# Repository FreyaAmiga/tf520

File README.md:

Terrible Fire 68020 "Accelerator"
=================================

** WARNING THIS IS BETA AT THE MOMENT

This repository contains all the files needed to produce a copy of my accelerator board.

The CPLD Required is a XC9532XL-VQ44

Everything in this repository is released under the GNU GPLv2. You may create or base commercial PCBs from the work in this repository but you must make the sources for all derivative work available. 

Firmware / Requirements
------------

  * Xilinx ISE, 14.7 (the final version - other versions may work but this is the one I support)
  * JTAG Adaptor

PCB Manufacture
---------------

You may get any PCB manufacturer to produce the board for you. The board is 2-layer. I recommend DirtyPCBs 

This link takes you to a store to buy them 

http://dirtypcbs.com/store/designer/details/12476/1120/sl520-rev3-zip

To populate a PCB you will likely need the following tools.

  * Soldering Station (with hot air rework and an iron - probably with a few tips)
  * Stereo Microscope (or similar for soldering under)
  * Bench Power Supply (to verify the regulator circuit)
 
There will be those with more experience and great eyesight that could manage it with just a soldering iron but I am trying to be realistic here.

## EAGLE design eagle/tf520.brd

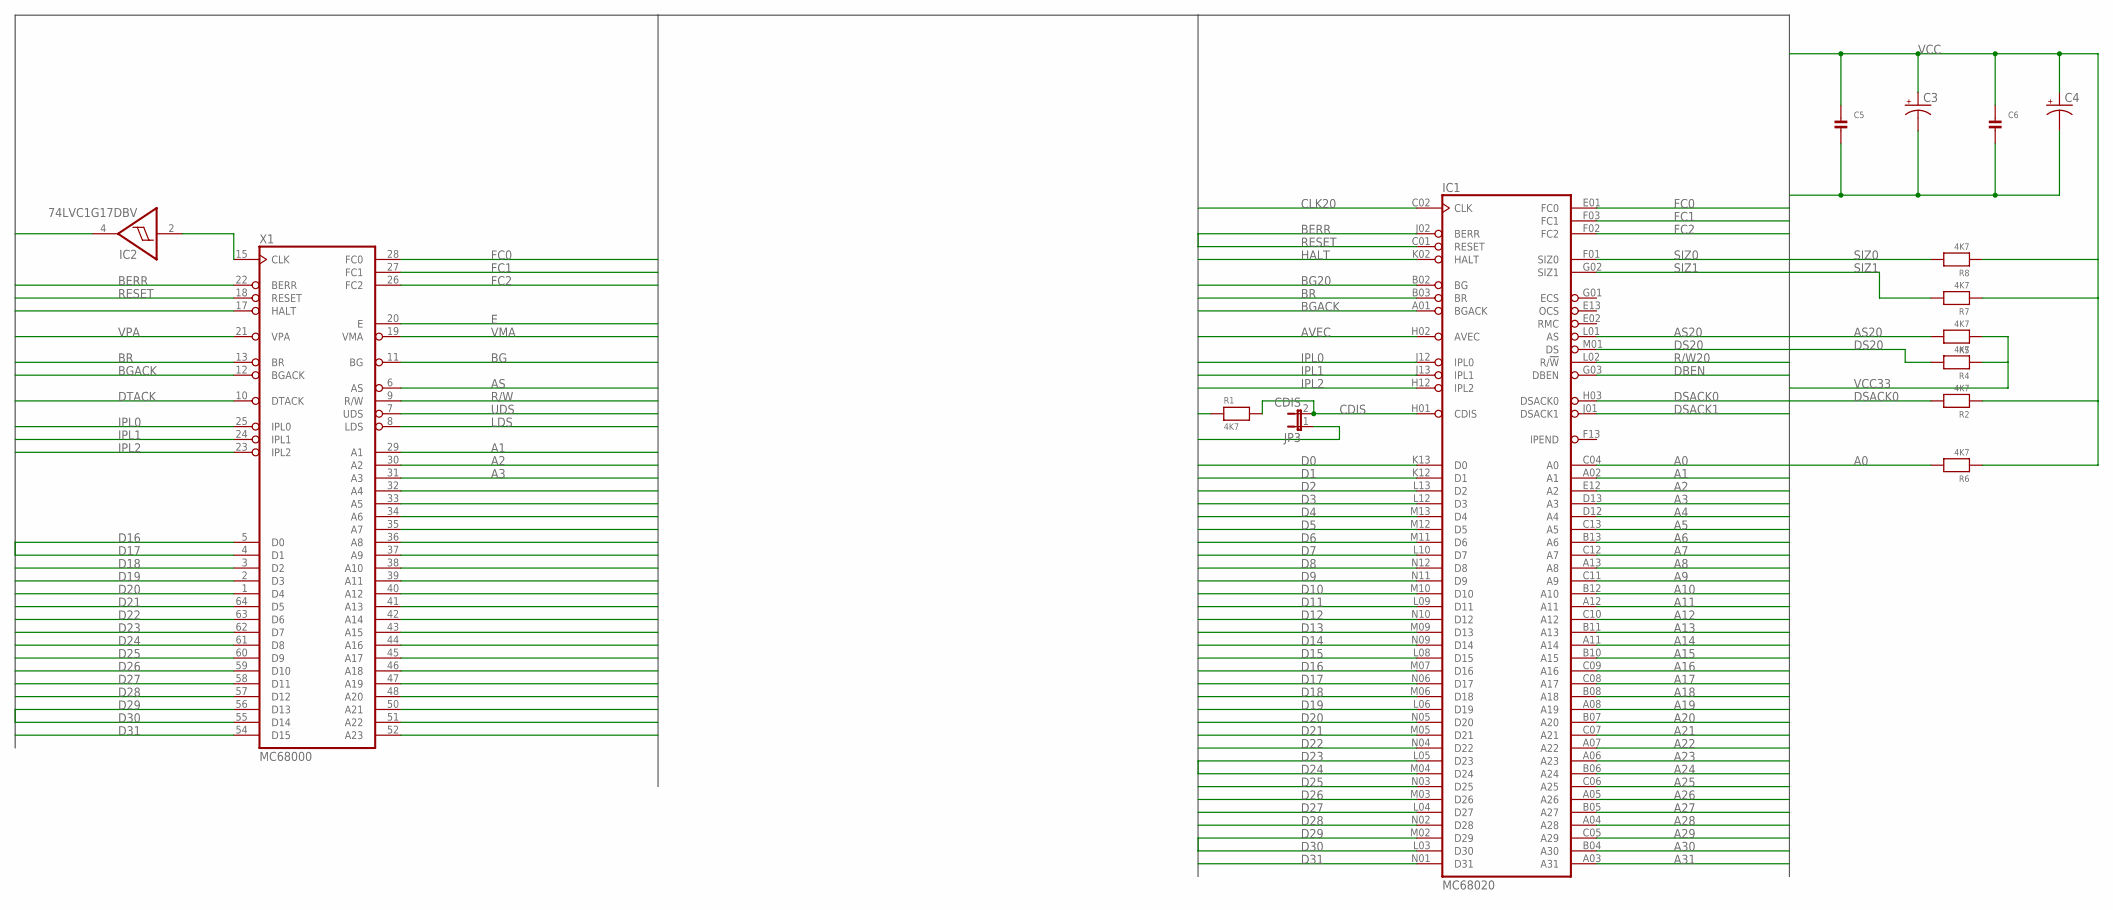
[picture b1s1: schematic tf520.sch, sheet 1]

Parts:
C3, C4: CAP_POLD; PANASONIC_D
C5, C6: CAP_CERAMIC1206; 1206
IC1: MC68020; MPGA114
IC2: 74LVC1G17DBV; SOT23-5
JP3: CDIS; 1X02
R1, R2, R4, R5, R6, R7, R8: 4K7; 1206
X1: MC68000; DIL64

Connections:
A0: IC1.C04 (A0), R6.2; also elsewhere on the board
A1: IC1.A02 (A1), X1.29 (A1)
A2: IC1.E12 (A2), X1.30 (A2)
A3: IC1.D13 (A3), X1.31 (A3)
A4: IC1.D12 (A4), X1.32 (A4)
A5: IC1.C13 (A5), X1.33 (A5)
A6: IC1.B13 (A6), X1.34 (A6)
A7: IC1.C12 (A7), X1.35 (A7)
A8: IC1.A13 (A8), X1.36 (A8)
A9: IC1.C11 (A9), X1.37 (A9)
A10: IC1.B12 (A10), X1.38 (A10)
A11: IC1.A12 (A11), X1.39 (A11)
A12: IC1.C10 (A12), X1.40 (A12)
A13: IC1.B11 (A13), X1.41 (A13)
A14: IC1.A11 (A14), X1.42 (A14)
A15: IC1.B10 (A15), X1.43 (A15)
A16: IC1.C09 (A16), X1.44 (A16); also elsewhere on the board
A17: IC1.C08 (A17), X1.45 (A17); also elsewhere on the board
A18: IC1.B08 (A18), X1.46 (A18); also elsewhere on the board
A19: IC1.A08 (A19), X1.47 (A19); also elsewhere on the board
A20: IC1.B07 (A20), X1.48 (A20)
A21: IC1.C07 (A21), X1.50 (A21)
A22: IC1.A07 (A22), X1.51 (A22)
A23: IC1.A06 (A23), X1.52 (A23)
A24: IC1.B06 (A24)
A25: IC1.C06 (A25)
A26: IC1.A05 (A26)
A27: IC1.B05 (A27)
A28: IC1.A04 (A28)
A29: IC1.C05 (A29)
A30: IC1.B04 (A30)
A31: IC1.A03 (A31)
AS: X1.6 (AS); also elsewhere on the board
AS20: IC1.L01 (AS), R5.2; also elsewhere on the board
AVEC: IC1.H02 (AVEC); also elsewhere on the board
BERR: IC1.J02 (BERR), X1.22 (BERR); also elsewhere on the board
BG: X1.11 (BG); also elsewhere on the board
BG20: IC1.B02 (BG); also elsewhere on the board
BGACK: IC1.A01 (BGACK), X1.12 (BGACK); also elsewhere on the board
BR: IC1.B03 (BR), X1.13 (BR)
CDIS: IC1.H01 (CDIS), JP3.2, R1.2
CLK7M: IC2.4 (O); also elsewhere on the board
CLK7M_RAW: IC2.2 (I), X1.15 (CLK)
CLK20: IC1.C02 (CLK); also elsewhere on the board
D0: IC1.K13 (D0)
D1: IC1.K12 (D1)
D2: IC1.L13 (D2)
D3: IC1.L12 (D3)
D4: IC1.M13 (D4)
D5: IC1.M12 (D5)
D6: IC1.M11 (D6)
D7: IC1.L10 (D7)
D8: IC1.N12 (D8)
D9: IC1.N11 (D9)
D10: IC1.M10 (D10)
D11: IC1.L09 (D11)
D12: IC1.N10 (D12)
D13: IC1.M09 (D13)
D14: IC1.N09 (D14)
D15: IC1.L08 (D15)
D16: IC1.M07 (D16), X1.5 (D0)
D17: IC1.N06 (D17), X1.4 (D1)
D18: IC1.M06 (D18), X1.3 (D2)
D19: IC1.L06 (D19), X1.2 (D3)
D20: IC1.N05 (D20), X1.1 (D4)
D21: IC1.M05 (D21), X1.64 (D5)
D22: IC1.N04 (D22), X1.63 (D6)
D23: IC1.L05 (D23), X1.62 (D7)
D24: IC1.M04 (D24), X1.61 (D8)
D25: IC1.N03 (D25), X1.60 (D9)
D26: IC1.M03 (D26), X1.59 (D10)
D27: IC1.L04 (D27), X1.58 (D11)
D28: IC1.N02 (D28), X1.57 (D12)
D29: IC1.M02 (D29), X1.56 (D13)
D30: IC1.L03 (D30), X1.55 (D14)
D31: IC1.N01 (D31), X1.54 (D15)
DBEN: IC1.G03 (DBEN)
DS20: IC1.M01 (DS), R4.2; also elsewhere on the board
DSACK0: IC1.H03 (DSACK0), R2.2
DSACK1: IC1.J01 (DSACK1); also elsewhere on the board
DTACK: X1.10 (DTACK); also elsewhere on the board
E: X1.20 (E); also elsewhere on the board
FC0: IC1.E01 (FC0), X1.28 (FC0); also elsewhere on the board
FC1: IC1.F03 (FC1), X1.27 (FC1); also elsewhere on the board
FC2: IC1.F02 (FC2), X1.26 (FC2); also elsewhere on the board
GND: C3.-, C4.-, C5.2, C6.2, IC1.A10 (GND), IC1.B01 (GND), IC1.B09 (GND), IC1.C03 (GND), IC1.F12 (GND), IC1.G12 (GND), IC1.H13 (GND), IC1.J03 (GND), IC1.K01 (GND), IC1.K03 (GND), IC1.L07 (GND), IC1.L11 (GND), IC1.N07 (GND), IC2.3 (GND), JP3.1, X1.16 (GND), X1.53 (GND); also elsewhere on the board
HALT: IC1.K02 (HALT), X1.17 (HALT); also elsewhere on the board
IPL0: IC1.J12 (IPL0), X1.25 (IPL0)
IPL1: IC1.J13 (IPL1), X1.24 (IPL1)
IPL2: IC1.H12 (IPL2), X1.23 (IPL2)
LDS: X1.8 (LDS); also elsewhere on the board
R/W: X1.9 (R/W); also elsewhere on the board
R/W20: IC1.L02 (R/!W); also elsewhere on the board
RESET: IC1.C01 (RESET), X1.18 (RESET); also elsewhere on the board
SIZ0: IC1.F01 (SIZ0), R8.2; also elsewhere on the board
SIZ1: IC1.G02 (SIZ1), R7.2; also elsewhere on the board
UDS: X1.7 (UDS); also elsewhere on the board
VCC: C3.+, C4.+, C5.1, C6.1, IC1.A09 (VCC), IC1.D01 (VCC), IC1.D02 (VCC), IC1.D03 (VCC), IC1.E03 (VCC), IC1.G11 (VCC), IC1.G13 (VCC), IC1.M08 (VCC), IC1.N08 (VCC), IC1.N13 (VCC), IC2.5 (VCC), R1.1, R2.1, R6.1, R7.1, R8.1, X1.14 (VCC), X1.49 (VCC); also elsewhere on the board
VCC33: R4.1, R5.1; also elsewhere on the board
VMA: X1.19 (VMA); also elsewhere on the board
VPA: X1.21 (VPA); also elsewhere on the board

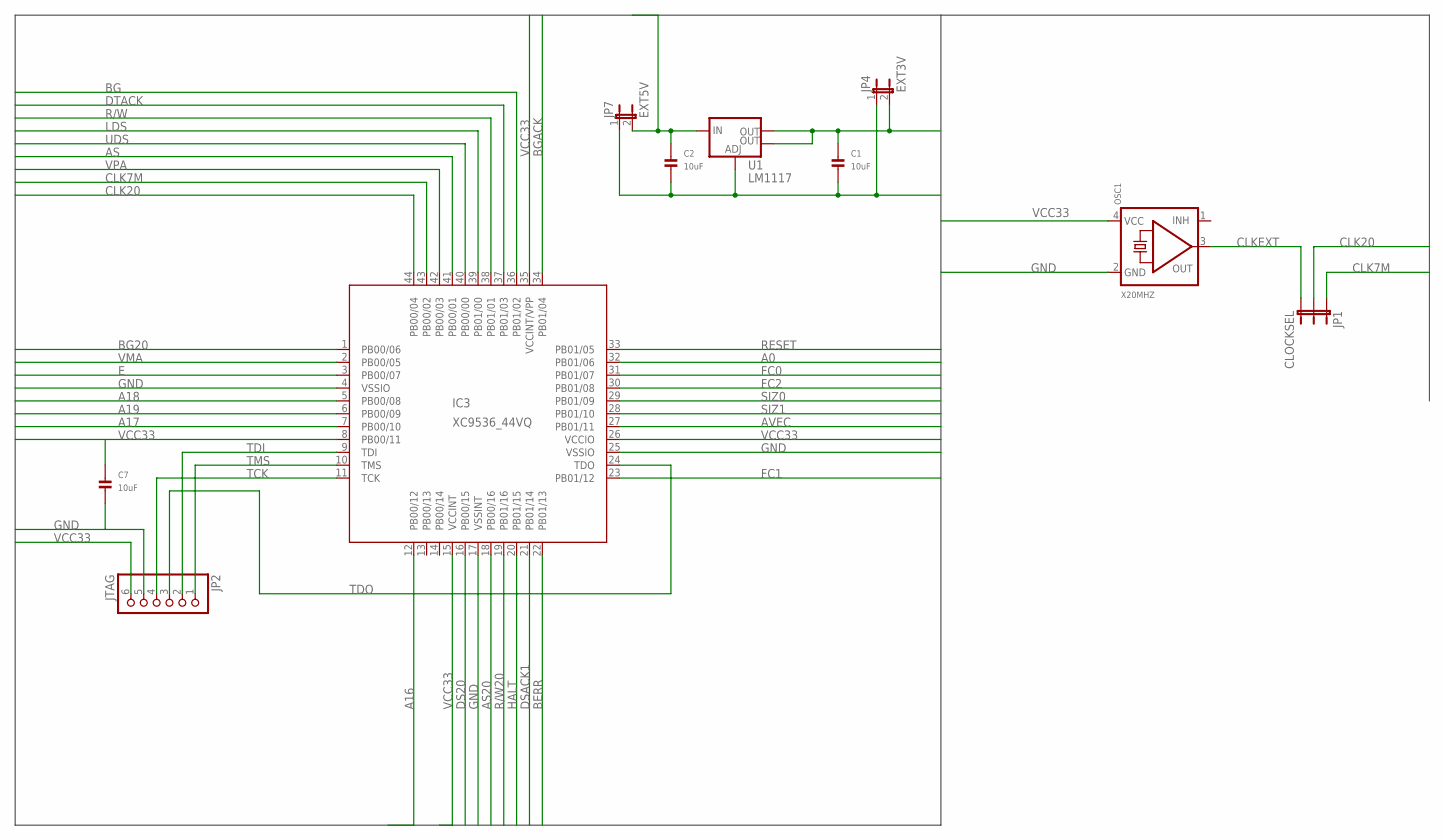
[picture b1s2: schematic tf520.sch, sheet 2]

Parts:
C1, C2, C7: 10uF; 1206
IC3: XC9536_44VQ; SQFP-S-10X10-44
JP1: CLOCKSEL; 1X03
JP2: JTAG; 1X06_ROUND
JP4: EXT3V; 1X02
JP7: EXT5V; JP1
OSC1: X20MHZ; OSC_7X5MM
U1: LM1117; SOT223

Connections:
A0: IC3.32 (PB01/06); also elsewhere on the board
A16: IC3.12 (PB00/12); also elsewhere on the board
A17: IC3.7 (PB00/10); also elsewhere on the board
A18: IC3.5 (PB00/08); also elsewhere on the board
A19: IC3.6 (PB00/09); also elsewhere on the board
AS: IC3.41 (PB00/01); also elsewhere on the board
AS20: IC3.18 (PB00/16); also elsewhere on the board
AVEC: IC3.27 (PB01/11); also elsewhere on the board
BERR: IC3.22 (PB01/13); also elsewhere on the board
BG: IC3.36 (PB01/02); also elsewhere on the board
BG20: IC3.1 (PB00/06); also elsewhere on the board
BGACK: IC3.34 (PB01/04); also elsewhere on the board
CLK7M: IC3.43 (PB00/02), JP1.1; also elsewhere on the board
CLK20: IC3.44 (PB00/04), JP1.2; also elsewhere on the board
CLKEXT: JP1.3, OSC1.3 (OUT)
DS20: IC3.16 (PB00/15); also elsewhere on the board
DSACK1: IC3.21 (PB01/14); also elsewhere on the board
DTACK: IC3.37 (PB01/03); also elsewhere on the board
E: IC3.3 (PB00/07); also elsewhere on the board
FC0: IC3.31 (PB01/07); also elsewhere on the board
FC1: IC3.23 (PB01/12); also elsewhere on the board
FC2: IC3.30 (PB01/08); also elsewhere on the board
GND: C1.2, C2.2, C7.2, IC3.4 (VSSIO), IC3.17 (VSSINT), IC3.25 (VSSIO), JP2.5, JP4.1, JP7.1, OSC1.2 (GND), U1.1 (ADJ); also elsewhere on the board
HALT: IC3.20 (PB01/15); also elsewhere on the board
LDS: IC3.39 (PB01/00); also elsewhere on the board
R/W: IC3.38 (PB01/01); also elsewhere on the board
R/W20: IC3.19 (PB01/16); also elsewhere on the board
RESET: IC3.33 (PB01/05); also elsewhere on the board
SIZ0: IC3.29 (PB01/09); also elsewhere on the board
SIZ1: IC3.28 (PB01/10); also elsewhere on the board
TCK: IC3.11 (TCK), JP2.4
TDI: IC3.9 (TDI), JP2.2
TDO: IC3.24 (TDO), JP2.3
TMS: IC3.10 (TMS), JP2.1
UDS: IC3.40 (PB00/00); also elsewhere on the board
VCC: C2.1, JP7.2, U1.3 (IN); also elsewhere on the board
VCC33: C1.1, C7.1, IC3.8 (PB00/11), IC3.15 (VCCINT), IC3.26 (VCCIO), IC3.35 (VCCINT/VPP), JP2.6, JP4.2, OSC1.4 (VCC), U1.2 (OUT), U1.4 (OUT); also elsewhere on the board
VMA: IC3.2 (PB00/05); also elsewhere on the board
VPA: IC3.42 (PB00/03); also elsewhere on the board

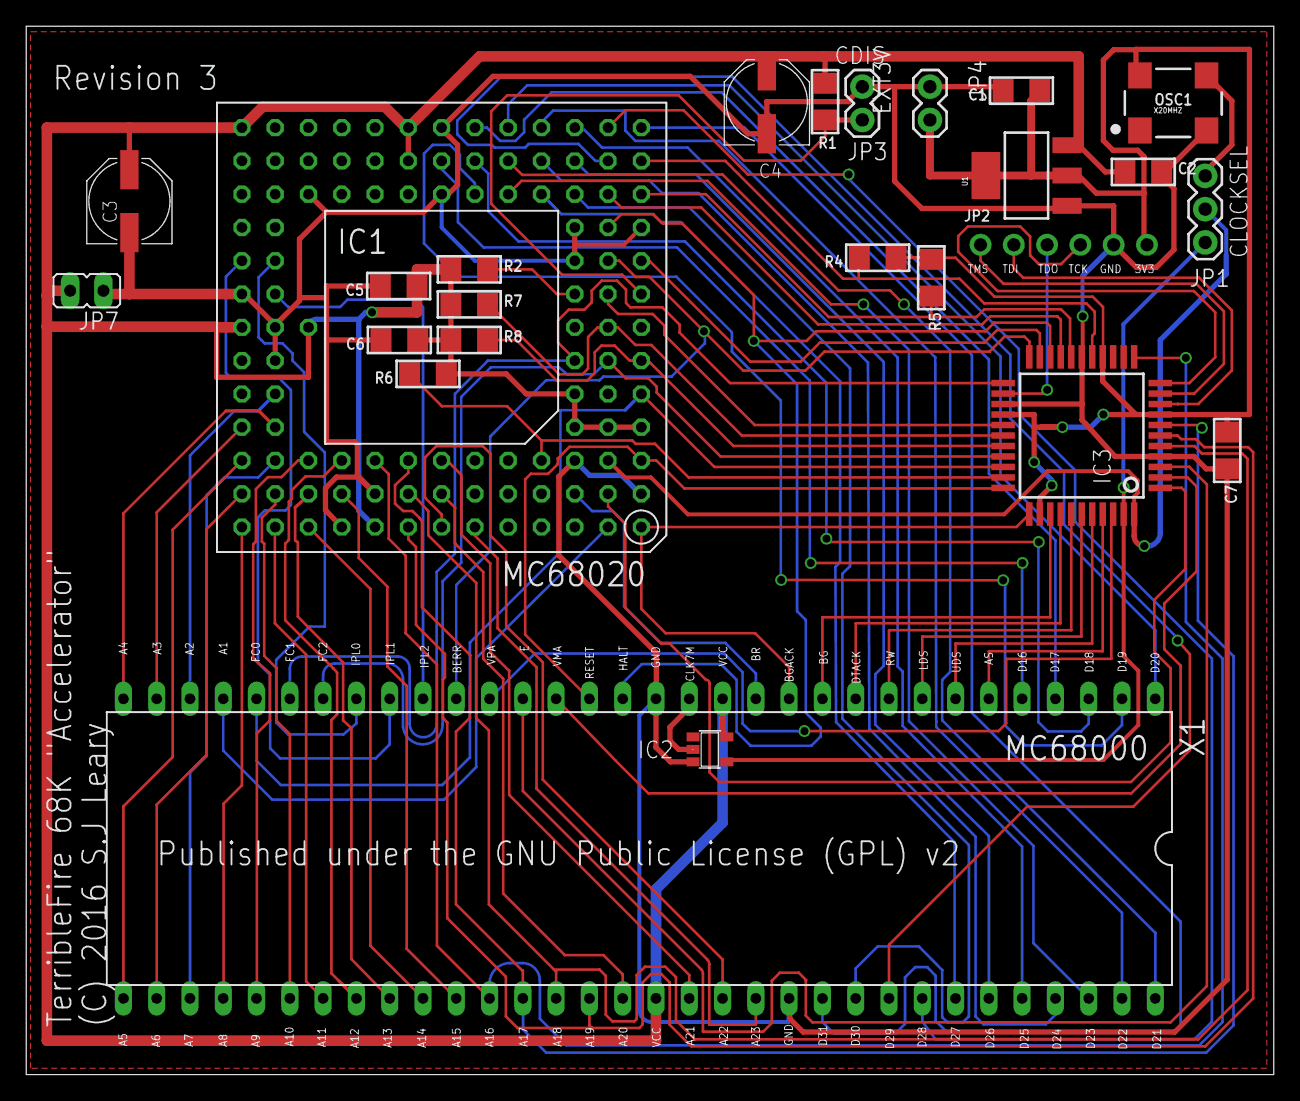
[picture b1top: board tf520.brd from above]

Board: 2 copper layers, 95.2 x 80.0 mm, 25 parts (0 on the bottom side), 81 nets.

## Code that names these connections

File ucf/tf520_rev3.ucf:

# 
# This file is part of the Terrible Fire Amiga Accelerator.
# 
# Copyright (c) 2016, Stephen J. Leary <stephen@terriblefire.com>
# 
# All rights reserved.
#
# This source file is free software: you can redistribute it and/or modify
# it under the terms of the GNU General Public License as published
# by the Free Software Foundation, either version 2 of the License, or
# (at your option) any later version.
# 
# This source file is distributed in the hope that it will be useful,
# but WITHOUT ANY WARRANTY; without even the implied warranty of
# MERCHANTABILITY or FITNESS FOR A PARTICULAR PURPOSE.  See the
# GNU General Public License for more details.
#
# You should have received a copy of the GNU General Public License
# along with this program.  If not, see <http://www.gnu.org/licenses/>.
#

#Clocks
NET "CLKCPU"    LOC = "P44" ;
NET "CLKCPU" BUFG=CLK;
NET "CLKCPU" TNM_NET = "CLKCPU"; # gives the net clk a group name as CLKCPU
TIMESPEC "TS_CLKCPU" = PERIOD "CLKCPU" 20 ns ; # add 20 ns PERIOD constraint the
OFFSET = IN 5 ns BEFORE "CLKCPU" ; # add  offset in constraint
OFFSET = OUT 5 ns AFTER "CLKCPU" ; # add  offset out constraint

NET "CLK7M"    LOC = "P43" ;
NET "CLK7M" BUFG=CLK;
NET "CLK7M" TNM_NET = "CLK7M"; # gives the net clk a group name as CLK7M
TIMESPEC "TS_CLK7M" = PERIOD "CLK7M" 139 ns ; # add 139 ns PERIOD constraint the
OFFSET = IN 15 ns BEFORE "CLK7M" ; # add  offset in constraint
OFFSET = OUT 15 ns AFTER "CLK7M" ; # add  offset out constraint

# 68K Signals
NET "VPA"    LOC = "P42";
NET "AS"     LOC = "P41";
NET "UDS"    LOC = "P40";
NET "LDS"    LOC = "P39";
NET "RW00"   LOC = "P38";
NET "DTACK"  LOC = "P37";
NET "BG"     LOC = "P36";
NET "BGACK"  LOC = "P34";
NET "VMA"    LOC = "P02" ;
NET "E"      LOC = "P03" ;
NET "BERR"   LOC = "P22";

NET "A0"    LOC = "P32";
NET "A<16>"	  LOC = "P12";
NET "A<17>"	  LOC = "P07";
NET "A<18>"	  LOC = "P05";
NET "A<19>"	  LOC = "P06";

# 68020 Signals

#NET "HALT"	  LOC = "P20";
#NET "RESET"  LOC = "P33" ;
#NET "HIGH"	  LOC = "P08" ; // do not drive low.

#NET "NC<0>"	  LOC = "P13" ;
#NET "NC<1>"	  LOC = "P14" ;


NET "BG20"	  LOC = "P01" ;
NET "DSACK1"  LOC = "P21" ;
NET "RW20"    LOC = "P19";
NET "AS20"	  LOC = "P18" ;
NET "DS20"	  LOC = "P16" ;

NET "AVEC"	  LOC = "P27" ;
NET "SIZ<1>"  LOC = "P28" ;
NET "SIZ<0>"  LOC = "P29" ;

NET "FC<0>"   LOC = "P31"  ;
NET "FC<1>"	  LOC = "P23" ;
NET "FC<2>"	  LOC = "P30" ;

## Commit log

2016-10-24 Initial file structure
2016-10-24 adding basic rtl/sim source files for revision 1
2016-10-24 renaming a few things and updating
2016-10-24 updaing stuff
2016-10-24 Committing the rev2 eagle files and the gerbers of rev1 and rev2
2016-12-18 Adding the Atari ST fixes Reorganizing the repos. Added jed files for rev 2 and rev 3 Published the REV 3 sources and ucf
2016-12-18 updated the pcb link

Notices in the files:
eagle/tf520.brd:
(C) 2016 S.J Leary
Published under the GNU Public License (GPL) v2
parts and their libraries:
microbuilder: This work is placed in the public domain, and may be freely used for commercial and non-commercial work with the following conditions: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
SparkFun-Retired: Licensing:Creative Commons ShareAlike 4.0 International - https://creativecommons.org/licenses/by-sa/4.0
